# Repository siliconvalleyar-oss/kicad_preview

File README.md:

# KiCad Preview

A professional **Flutter** application for previewing KiCad schematic (`.kicad_sch`) and PCB (`.kicad_pcb`) files. Features a minimal, KiCad-inspired interface with layer visualization, hierarchical navigation, BOM extraction, and collaborative tools.

## Features

- **Schematic Viewer** — Render symbols, wires, labels, and hierarchical sheets with zoom/pan gestures
- **PCB Viewer** — Multi-layer PCB visualization with proper KiCad v7 layer colors, side toggle, and flip view
- **Layer Control** — Toggle individual layers or use quick presets (Basic, All, None)
- **Hierarchy Navigation** — Tree view of hierarchical sheet structure with sub-sheet loading
- **BOM Extraction** — Bill of Materials with CSV export
- **Notes / Chat Panel** — Add notes with auto-insert of component references in chat mode; export/share notes
- **Properties Panel** — Floating card showing basic properties of the selected component
- **Element Selection** — Click to highlight components and traces; non-selected elements dim
- **Responsive Toolbar** — Icons only in portrait, full labels in landscape
- **File Loading** — Open `.kicad_sch` and `.kicad_pcb` files from bundled assets or device storage

## Getting Started

### Prerequisites
- Flutter SDK 3.44.1+
- Dart SDK 3.12.1+

### Installation

```bash
git clone <repository-url>
cd kicad_preview
flutter pub get
flutter run
```

### Opening Files
- The demo project (`project_pi`) loads automatically on startup with both schematic and PCB
- Tap the folder icon to browse bundled projects or pick files from device storage
- Switch between Schematic, PCB, and BOM views using the toolbar

## Project Structure

```
lib/
├── main.dart                  # App entry point
├── controllers/
│   └── app_state.dart         # State management (ChangeNotifier)
├── models/
│   ├── schematic.dart         # Schematic data model
│   ├── schematic_element.dart  # Element, sheet, wire, junction types
│   ├── pcb.dart               # PCB data model
│   └── pcb_element.dart       # Layer, footprint, track, via types
├── parsers/
│   ├── sexpr_parser.dart      # S-expression parser (KiCad format)
│   ├── schematic_parser.dart  # .kicad_sch parser + BOM generation
│   └── pcb_parser.dart        # .kicad_pcb parser
├── views/
│   ├── splash_screen.dart     # Animated splash with logo
│   ├── main_view.dart         # Main layout with panels and canvas
│   ├── schematic_view.dart    # Schematic rendering (CustomPainter)
│   ├── pcb_view.dart          # PCB rendering with layer control
│   └── bom_view.dart          # Bill of Materials table view
└── widgets/
    ├── toolbar.dart           # Responsive toolbar
    ├── hierarchy_panel.dart   # Sheet navigation tree
    ├── layer_panel.dart       # Layer toggles with presets
    ├── notes_panel.dart       # Notes / Chat panel
    └── properties_panel.dart  # Selected element properties
```

## Version

Current version: **1.1.2** <!-- MUST match VERSION file -->

## License

This project is licensed under the MIT License.

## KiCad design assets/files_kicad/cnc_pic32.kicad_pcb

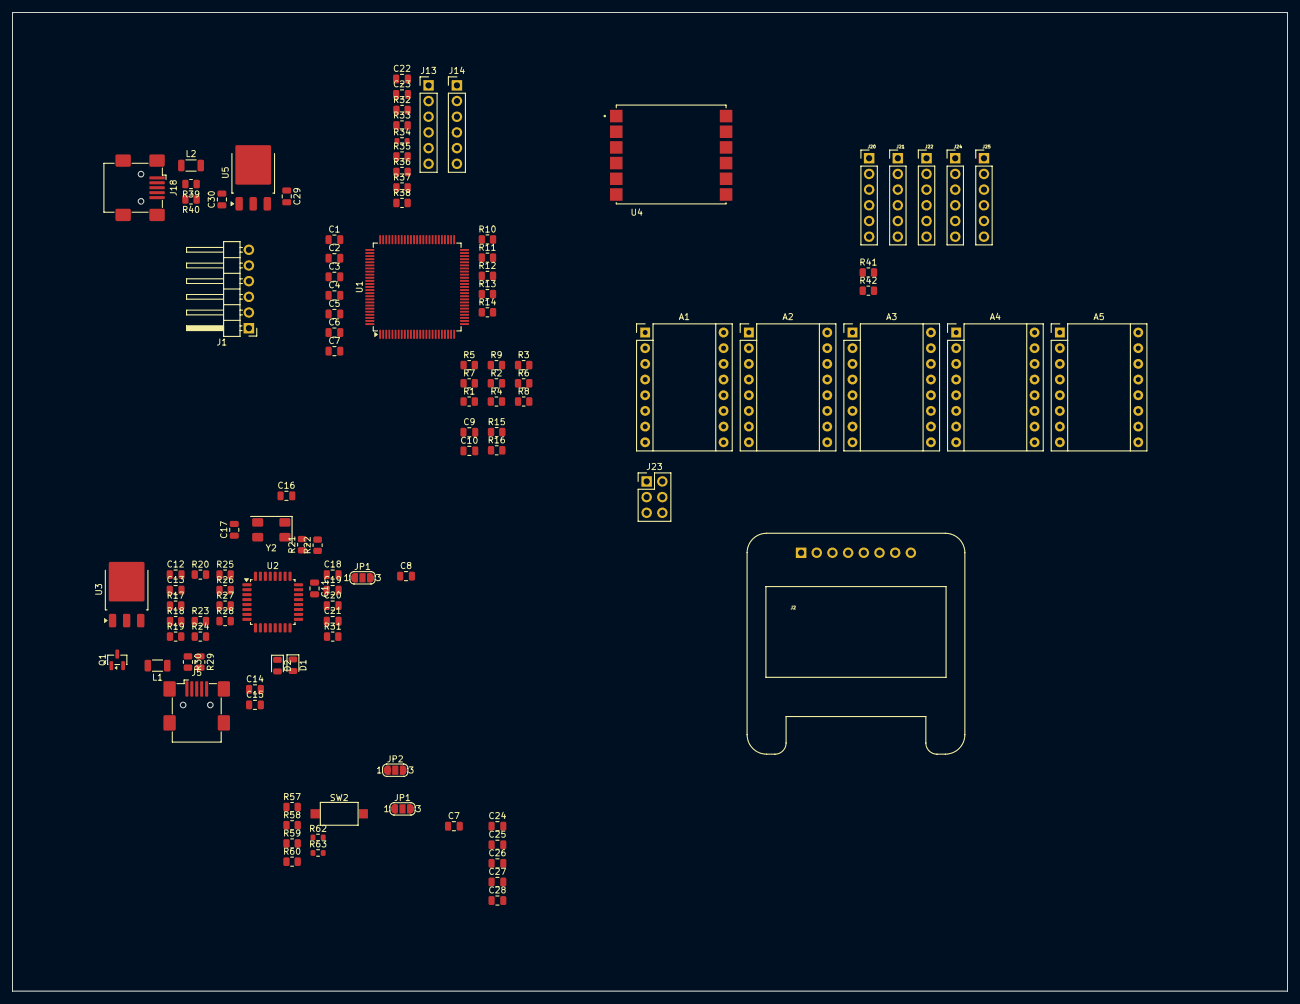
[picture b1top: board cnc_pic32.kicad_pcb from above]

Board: 4 copper layers, 206.5 x 158.5 mm, 111 parts (0 on the bottom side), 72 nets, no tracks yet.

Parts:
A1, A2, A3, A4, A5: Pololu_Breakout_A4988; Pololu_Breakout-16_15.2x20.3mm
C1, C2, C3, C4, C5, C6, C7, C7#2, C8, C11, C14, C15, C18, C19, C20, C21, C22, C23, C24, C25, C26, C27, C28, C29, C30: 100nf; C_0805_2012Metric
C9, C10, C16, C17: 15p; C_0805_2012Metric
C12, C13: 33nf; C_0805_2012Metric
D1, D2: RX; D_0805_2012Metric
J1: icd; PinHeader_1x06_P2.54mm_Horizontal
J2: ST7789 oled 128x64; Adafruit_SSD1306_No_Mounting_Holes_pads
J5, J18: USB_B_Mini; USB_Mini-B_Wuerth_65100516121_Horizontal
J13, J14: mrf24j40_tp; PinHeader_1x06_P2.54mm_Vertical
J20, J21, J22, J24, J25: pololu; PinHeader_1x06_P2.54mm_Vertical
J23: conector oled ST1306 128x32; PinHeader_2x03_P2.54mm_Vertical
JP1, JP1#2, JP2: SolderJumper_3_Bridged123; SolderJumper-3_P1.3mm_Open_RoundedPad1.0x1.5mm_NumberLabels
L1, L2: 100mh; L_1206_3216Metric
Q1: 2N7002; SOT-23
R1, R2, R7, R8, R14, R21, R22: 100; R_0805_2012Metric
R3, R10, R13, R17, R18, R19, R20, R23, R24, R26, R31: 10K; R_0805_2012Metric
R4, R6, R39, R40: 22; R_0805_2012Metric
R5, R9, R41, R42: 1k; R_0805_2012Metric
R11, R12: 0; R_0805_2012Metric
R15: 1K; R_0805_2012Metric
R16: 1M; R_0805_2012Metric
R25, R27: 1K5; R_0805_2012Metric
R28: 4K7; R_0805_2012Metric
R29, R30: 27; R_0805_2012Metric
R32, R33, R35, R36, R37, R38, R57, R58, R59, R60: 2k2; R_0805_2012Metric
R34, R62, R63: 2k2; R_0603_1608Metric
SW2: up; SW_SPST_CK_RS282G05A3
U1: PIC32MX795F512L-80x-PF; TQFP-100_14x14mm_P0.5mm
U2: FT232BM; LQFP-32_7x7mm_P0.8mm
U3, U5: LM1117DT-3.3; TO-252-3_TabPin2
U4: MRF24J40MA; MODULE_MRF24J40MA
Y2: 6MHZ; Crystal_SMD_0603-4Pin_6.0x3.5mm

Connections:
+3.3V: A1.8 (VMOT), A2.8 (VMOT), A3.8 (VMOT), A4.8 (VMOT), A5.8 (VMOT), C1.1, C2.1, C3.1, C4.1, C5.1, C8.1, C22.1, C23.1, C24.1, C25.1, C26.1, C27.1, C28.1, J1.2, J2.2, J14.3, J23.2, R10.1, R32.1, R33.1, R35.2, R36.2, R37.1, R38.1, R41.1, R42.1, R57.1, R58.1, R62.1, R63.1, U1.2 (VDD), U1.16 (VDD), U1.30 (AVDD), U1.37 (VDD), U1.46 (VDD), U1.55 (VUSB3V3), U1.62 (VDD), U1.85 (VCAP/VDDCORE), U1.86 (VDD), U4.10 (VIN)
+3V3: C15.2, C18.1, C19.1, C20.2, C21.2, C30.2, R20.1, R23.1, R24.1, R31.1, U2.13 (VCCIO), U3.2 (VO), U5.2 (VO)
+5V: A1.2 (VDD), A2.2 (VDD), A3.2 (VDD), A4.2 (VDD), A5.2 (VDD)
/Ft232/FT: R18.2, U2.14 (PWRCTL)
/Ft232/FT_CTS: C11.2, U2.22 (D3/~CTS)
/Ft232/FT_PWR_EN: R19.1, U2.15 (~PWREN)
/Ft232/FT_RESET: R26.2, R28.2, U2.4 (~RESET)
/Ft232/FT_RST_OUT: R27.1, U2.5 (~RSTOUT)
/Ft232/FT_USB_BM: R29.1, U2.8 (USBDM)
/Ft232/FT_USB_DP: R27.2, R30.1, U2.7 (USBDP)
/Ft232/FT_XTIN: C16.1, U2.27 (XTIN), Y2.1
/Ft232/FT_XTOUT: C17.1, U2.28 (XTOUT), Y2.3
/Ft232/RX_MCU: JP2.2 (C), R21.2
/Ft232/TX_MCU: JP1.2 (C), R22.2
/Ft232/V+_USB: C14.2, L1.2, R17.2, R25.2, R28.1, U2.3 (VCC), U2.26 (VCC), U3.3 (VI)
/Ft232/mclr: C11.1, J1.1, R10.2, U1.13 (~MCLR)
/MCU/RB6: J1.5, U1.26 (PGEC2/RB6)
/MCU/RB7: J1.4, U1.27 (PGED2/RB7)
/MCU/RD0: R11.1, U1.72 (RD0)
/MCU/RD1: R12.1, U1.76 (RD1)
/Oled/scl: J2.4, J23.3, R42.2
/Oled/sda: J2.3, J23.4, R41.2
/oscilator/OSC1: C10.1, R16.2
/zigbee/CS_spi4: J14.5, R36.1, U4.8 (~CS)
/zigbee/MISO_spi4: J14.6, R35.1, U4.7 (SDO)
/zigbee/MOSI_spi4: J13.5, R38.2, U4.5 (SDI)
/zigbee/RESET_mrf: J13.2, R32.2, U4.2 (~RESET)
/zigbee/SCK_spi4: J13.6, R37.2, U4.6 (SCK)
/zigbee/WAKE_mrf: J13.3, R34.1, U4.3 (WAKE)
/zigbee/int: J13.4, R33.2, U4.4 (INT)
GND: A1.1 (GND), A1.7 (GND), A2.1 (GND), A2.7 (GND), A3.1 (GND), A4.1 (GND), A4.7 (GND), A5.1 (GND), A5.7 (GND), C1.2, C2.2, C3.2, C4.2, C5.2, C8.2, C9.2, C10.2, C12.2, C13.2, C14.1, C15.1, C16.2, C17.2, C18.2, C19.2, C20.1, C21.1, C22.2, C23.2, C24.2, C25.2, C26.2, C27.2, C28.2, C29.1, C30.1, J1.3, J2.1, J5.5 (GND), J13.1, J14.1, J14.2, J18.5 (GND), J23.1, Q1.2 (S), R18.1, R26.1, R34.2, R60.2, SW2.2, U1.15 (VSS), U1.31 (AVSS), U1.36 (VSS), U1.45 (VSS), U1.65 (VSS), U1.75 (VSS), U2.9 (GND), U2.17 (GND), U2.29 (AGND), U2.31 (TEST), U3.1 (GND), U4.1 (GND), U4.11 (GND), U4.12 (GND), U5.1 (GND), Y2.2, Y2.4
unnamed: A1.4 (1A), J25.3
unnamed: A1.3 (1B), J25.4
unnamed: A1.5 (2A), J25.2
unnamed: A1.6 (2B), J25.1
unnamed: A2.4 (1A), J20.3
unnamed: A2.3 (1B), J20.4
unnamed: A2.5 (2A), J20.2
unnamed: A2.6 (2B), J20.1
unnamed: A3.4 (1A), J24.3
unnamed: A3.3 (1B), J24.4
unnamed: A3.5 (2A), J24.2
unnamed: A3.6 (2B), J24.1
unnamed: A4.4 (1A), J22.3
unnamed: A4.3 (1B), J22.4
unnamed: A4.5 (2A), J22.2
unnamed: A4.6 (2B), J22.1
unnamed: A5.4 (1A), J21.3
unnamed: A5.3 (1B), J21.4
unnamed: A5.5 (2A), J21.2
unnamed: A5.6 (2B), J21.1
unnamed: C9.1, R15.2, R16.1
unnamed: D1.2 (A), R20.2
unnamed: D1.1 (K), U2.12 (~TXLED)
unnamed: D2.2 (A), R23.2
unnamed: D2.1 (K), U2.11 (~RXLED)
unnamed: C13.1, U2.6 (3V3OUT)
unnamed: J5.1 (VBUS), L1.1
unnamed: J5.3 (D+), R29.2
unnamed: J5.2 (D-), R30.2
unnamed: J18.3 (D+), R39.2
unnamed: J18.2 (D-), R40.2
unnamed: J18.1 (VBUS), L2.1
unnamed: Q1.3 (D), R17.1
unnamed: Q1.1 (G), R19.2
unnamed: R58.2, SW2.1
unnamed: C29.2, L2.2, U5.3 (VI)
unnamed: C12.1, R25.1, U2.30 (AVCC)
unnamed: R21.1, U2.25 (D0/TXD)
unnamed: R22.1, U2.24 (D1/RXD)
unnamed: R24.2, U2.10 (~SLEEP)
TXD: JP1.1 (A), JP1#2.1 (A)
